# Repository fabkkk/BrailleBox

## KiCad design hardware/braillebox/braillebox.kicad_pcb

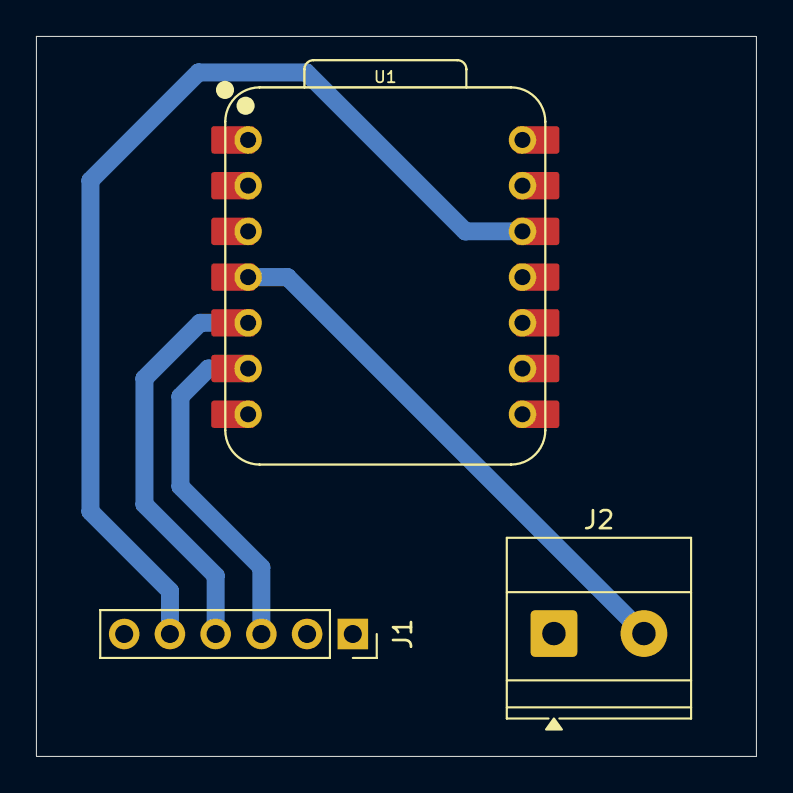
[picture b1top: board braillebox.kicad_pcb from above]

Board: 2 copper layers, 40.0 x 40.0 mm, 3 parts (0 on the bottom side), 5 nets.

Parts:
J1: PCA9685; PinSocket_1x06_P2.54mm_Vertical
J2: Botão; TerminalBlock_Phoenix_MKDS-1,5-2_1x02_P5.00mm_Horizontal
U1: XIAO-ESP32-S3-DIP

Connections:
+3.3V: J1.5, U1.12 (3V3)
GND: J1.1, J2.1, U1.13 (GND)
unnamed: J1.3, U1.6 (GPIO6_A5_D5_SCL)
unnamed: J1.4, U1.5 (GPIO5_A4_D4_SDA)
unnamed: J2.2, U1.4 (GPIO4_A3_D3)

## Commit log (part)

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2026-06-22 Add embebbed_software PlatformIO project
    Initialize an embedded PlatformIO project (embebbed_software) for the seeed_xiao_esp32s3 board. Adds project config (platformio.ini) with Adafruit PWM dependency, .gitignore and VSCode recommended ex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
2026-06-22 Add KiCAD project
2026-06-23 Make circuit
